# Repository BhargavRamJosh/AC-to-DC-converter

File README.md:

# AC to DC Converter (12V AC to DC)

## 🔌 Project Overview
This project demonstrates the design of a **12V AC to DC Converter** using a **bridge rectifier, filter capacitor, and indicator LED**. The goal is to provide a **stable DC voltage output** suitable for powering low-power electronic circuits such as **Arduino boards, sensors, or basic embedded modules**.

---

## 📷 Project Images

| PCB Routing (Top View) | Schematic (KiCad) | 3D View |
|------------------------|-------------------|---------|
|  |  |  |

---

## ⚙ Circuit Working

| Stage | Component | Purpose |
|--------|-----------|---------|
| AC Input | Screw Terminal (J102) | Connect 12V AC from transformer |
| Rectification | 4× 1N4007 Diodes | Converts AC to pulsating DC |
| Filtering | 1000µF Capacitor (C101) | Smooths the DC output |
| Indicator | LED + 2.2k Resistor (R101) | Shows power status |
| Output | Screw Terminal (J101) | Provides DC Output |

---

## ✅ Features

- Converts **12V AC to smooth DC**
- Compact **single-layer PCB layout**
- **Visual power indicator (LED)**
- **DIY-friendly through-hole components**

---

## 🧾 Components List

| Component | Value / Type | Quantity |
|-----------|---------------|----------|
| Diodes | 1N4007 | 4 |
| Capacitor | 1000µF / 25V | 1 |
| Resistor | 2.2kΩ | 1 |
| LED | Red / 5mm | 1 |
| Terminal Block | 2-Pin | 2 |

---

## 🛠 Applications

- Power supply for **Arduino / ESP32**
- **Sensor modules**
- **Small lab experiments**
- **Testing DC circuits from AC source**

---

## 🧑‍💻 Author

**Bhargav Ram**  
Electronics & Communication Engineering  
Passionate about **Embedded Systems & PCB Design**

---

If you like this project, ⭐ the repo or suggest improvements!

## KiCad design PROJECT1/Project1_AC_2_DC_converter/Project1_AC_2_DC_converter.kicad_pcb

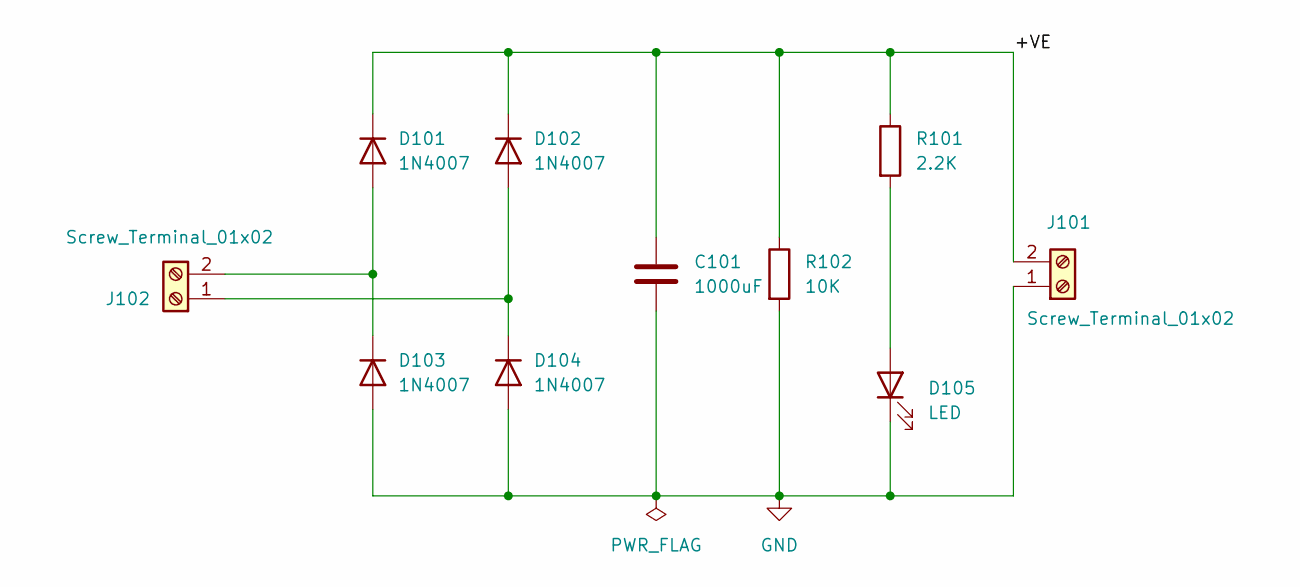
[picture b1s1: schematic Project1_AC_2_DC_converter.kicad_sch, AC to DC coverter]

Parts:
C101: 1000uF; C_Radial_D8.0mm_H11.5mm_P3.50mm
D101, D102, D103, D104: 1N4007; D_DO-41_SOD81_P10.16mm_Horizontal
D105: LED; LED_D5.0mm
J101, J102: Screw_Terminal_01x02; TerminalBlock_bornier-2_P5.08mm
R101: 2.2K; R_Axial_DIN0207_L6.3mm_D2.5mm_P7.62mm_Horizontal
R102: 10K; R_Axial_DIN0207_L6.3mm_D2.5mm_P7.62mm_Horizontal

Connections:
/+VE: C101.1, D101.1 (K), D102.1 (K), J101.2, R101.1, R102.1
GND: C101.2, D103.2 (A), D104.2 (A), D105.1 (K), J101.1, R102.2
unnamed: D101.2 (A), D103.1 (K), J102.2
unnamed: D102.2 (A), D104.1 (K), J102.1
unnamed: D105.2 (A), R101.2

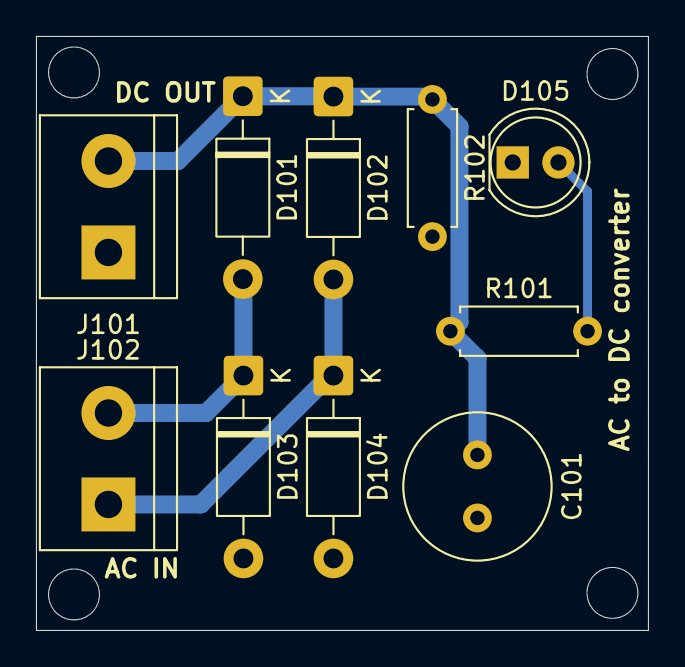
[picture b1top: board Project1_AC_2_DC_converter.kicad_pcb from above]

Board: 2 copper layers, 34.0 x 33.0 mm, 10 parts (0 on the bottom side), 5 nets.
